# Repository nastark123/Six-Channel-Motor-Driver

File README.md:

# Six-Channel-Motor-Driver
Design files for six channel motor driver.

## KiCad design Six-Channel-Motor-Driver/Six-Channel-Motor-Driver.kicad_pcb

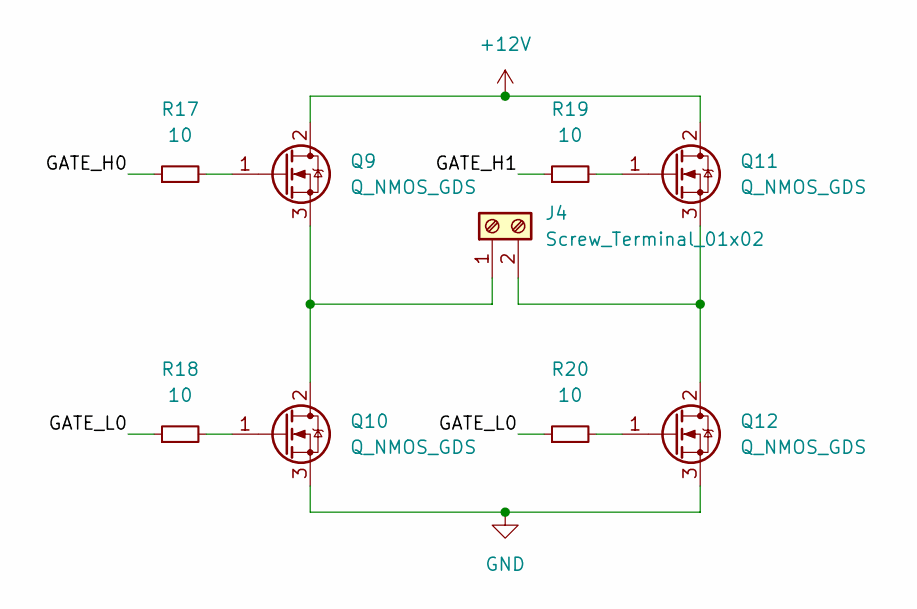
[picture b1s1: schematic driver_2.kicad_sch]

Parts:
J4: Screw_Terminal_01x02; SolderWire-2.5sqmm_1x02_P8.8mm_D2.4mm_OD4.4mm
Q9, Q10, Q11, Q12: Q_NMOS_GDS; SOT-23
R17, R18, R19, R20: 10; R_0603_1608Metric

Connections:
+12V: Q9.2 (D), Q11.2 (D); also elsewhere on the board
/Driver 2/GATE_H0: R17.1
/Driver 2/GATE_H1: R19.1
/Driver 2/GATE_L0: R18.1, R20.1
GND: Q10.3 (S), Q12.3 (S); also elsewhere on the board
unnamed: J4.1, Q9.3 (S), Q10.2 (D)
unnamed: J4.2, Q11.3 (S), Q12.2 (D)
unnamed: Q9.1 (G), R17.2
unnamed: Q10.1 (G), R18.2
unnamed: Q11.1 (G), R19.2
unnamed: Q12.1 (G), R20.2

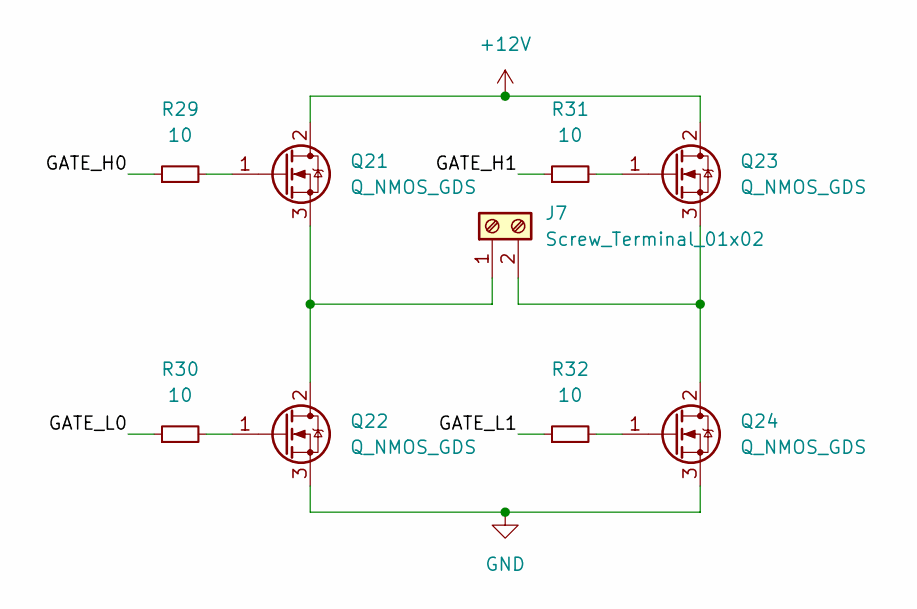
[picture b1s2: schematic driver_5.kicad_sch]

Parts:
J7: Screw_Terminal_01x02; SolderWire-2.5sqmm_1x02_P8.8mm_D2.4mm_OD4.4mm
Q21, Q22, Q23, Q24: Q_NMOS_GDS; SOT-23
R29, R30, R31, R32: 10; R_0603_1608Metric

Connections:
+12V: Q21.2 (D), Q23.2 (D); also elsewhere on the board
/Driver 5/GATE_H0: R29.1
/Driver 5/GATE_H1: R31.1
/Driver 5/GATE_L0: R30.1
/Driver 5/GATE_L1: R32.1
GND: Q22.3 (S), Q24.3 (S); also elsewhere on the board
unnamed: J7.1, Q21.3 (S), Q22.2 (D)
unnamed: J7.2, Q23.3 (S), Q24.2 (D)
unnamed: Q21.1 (G), R29.2
unnamed: Q22.1 (G), R30.2
unnamed: Q23.1 (G), R31.2
unnamed: Q24.1 (G), R32.2

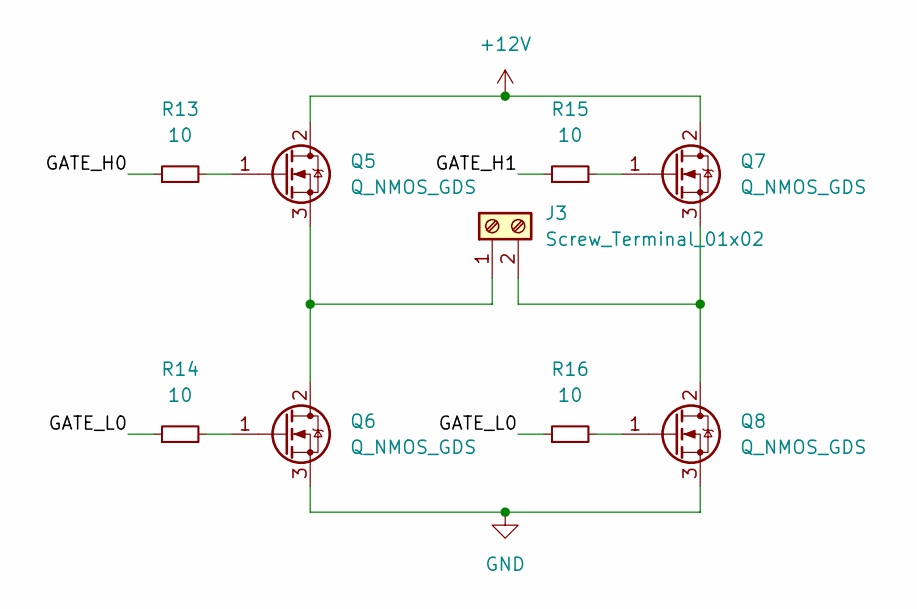
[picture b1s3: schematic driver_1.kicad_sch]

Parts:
J3: Screw_Terminal_01x02; SolderWire-2.5sqmm_1x02_P8.8mm_D2.4mm_OD4.4mm
Q5, Q6, Q7, Q8: Q_NMOS_GDS; SOT-23
R13, R14, R15, R16: 10; R_0603_1608Metric

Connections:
+12V: Q5.2 (D), Q7.2 (D); also elsewhere on the board
/Driver 1/GATE_H0: R13.1
/Driver 1/GATE_H1: R15.1
/Driver 1/GATE_L0: R14.1, R16.1
GND: Q6.3 (S), Q8.3 (S); also elsewhere on the board
unnamed: J3.1, Q5.3 (S), Q6.2 (D)
unnamed: J3.2, Q7.3 (S), Q8.2 (D)
unnamed: Q5.1 (G), R13.2
unnamed: Q6.1 (G), R14.2
unnamed: Q7.1 (G), R15.2
unnamed: Q8.1 (G), R16.2

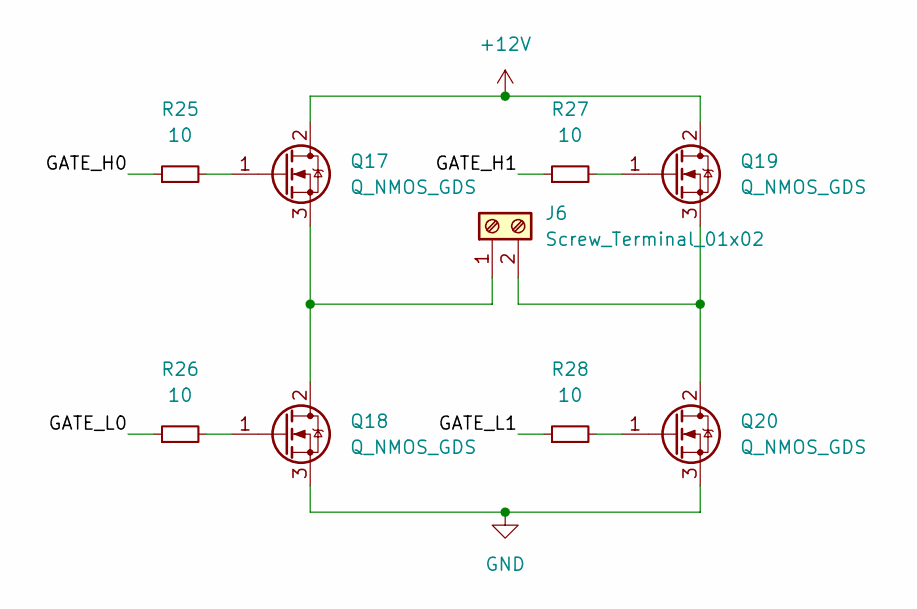
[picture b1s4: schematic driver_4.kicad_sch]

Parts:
J6: Screw_Terminal_01x02; SolderWire-2.5sqmm_1x02_P8.8mm_D2.4mm_OD4.4mm
Q17, Q18, Q19, Q20: Q_NMOS_GDS; SOT-23
R25, R26, R27, R28: 10; R_0603_1608Metric

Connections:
+12V: Q17.2 (D), Q19.2 (D); also elsewhere on the board
/Driver 4/GATE_H0: R25.1
/Driver 4/GATE_H1: R27.1
/Driver 4/GATE_L0: R26.1
/Driver 4/GATE_L1: R28.1
GND: Q18.3 (S), Q20.3 (S); also elsewhere on the board
unnamed: J6.1, Q17.3 (S), Q18.2 (D)
unnamed: J6.2, Q19.3 (S), Q20.2 (D)
unnamed: Q17.1 (G), R25.2
unnamed: Q18.1 (G), R26.2
unnamed: Q19.1 (G), R27.2
unnamed: Q20.1 (G), R28.2

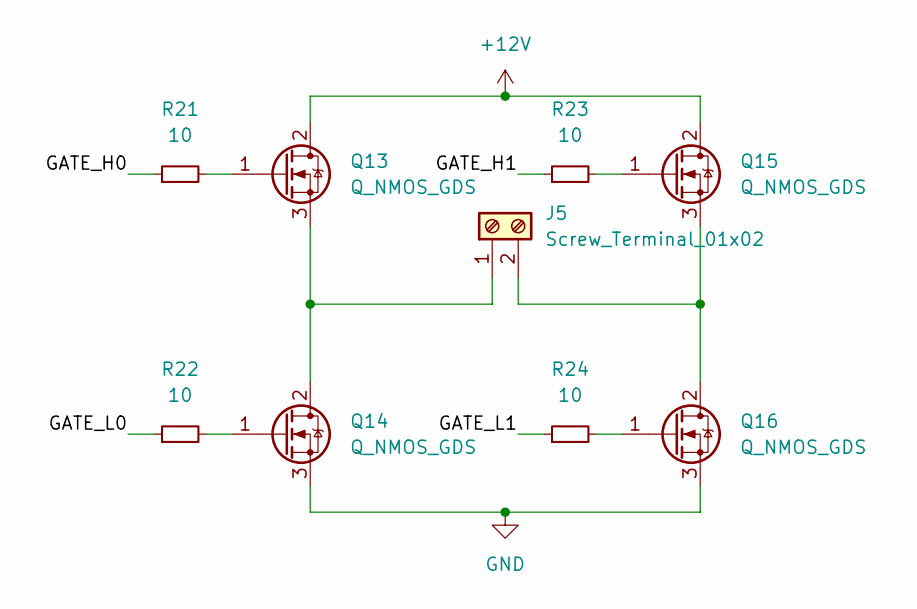
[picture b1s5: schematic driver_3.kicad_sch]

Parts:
J5: Screw_Terminal_01x02; SolderWire-2.5sqmm_1x02_P8.8mm_D2.4mm_OD4.4mm
Q13, Q14, Q15, Q16: Q_NMOS_GDS; SOT-23
R21, R22, R23, R24: 10; R_0603_1608Metric

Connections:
+12V: Q13.2 (D), Q15.2 (D); also elsewhere on the board
/Driver 3/GATE_H0: R21.1
/Driver 3/GATE_H1: R23.1
/Driver 3/GATE_L0: R22.1
/Driver 3/GATE_L1: R24.1
GND: Q14.3 (S), Q16.3 (S); also elsewhere on the board
unnamed: J5.1, Q13.3 (S), Q14.2 (D)
unnamed: J5.2, Q15.3 (S), Q16.2 (D)
unnamed: Q13.1 (G), R21.2
unnamed: Q14.1 (G), R22.2
unnamed: Q15.1 (G), R23.2
unnamed: Q16.1 (G), R24.2

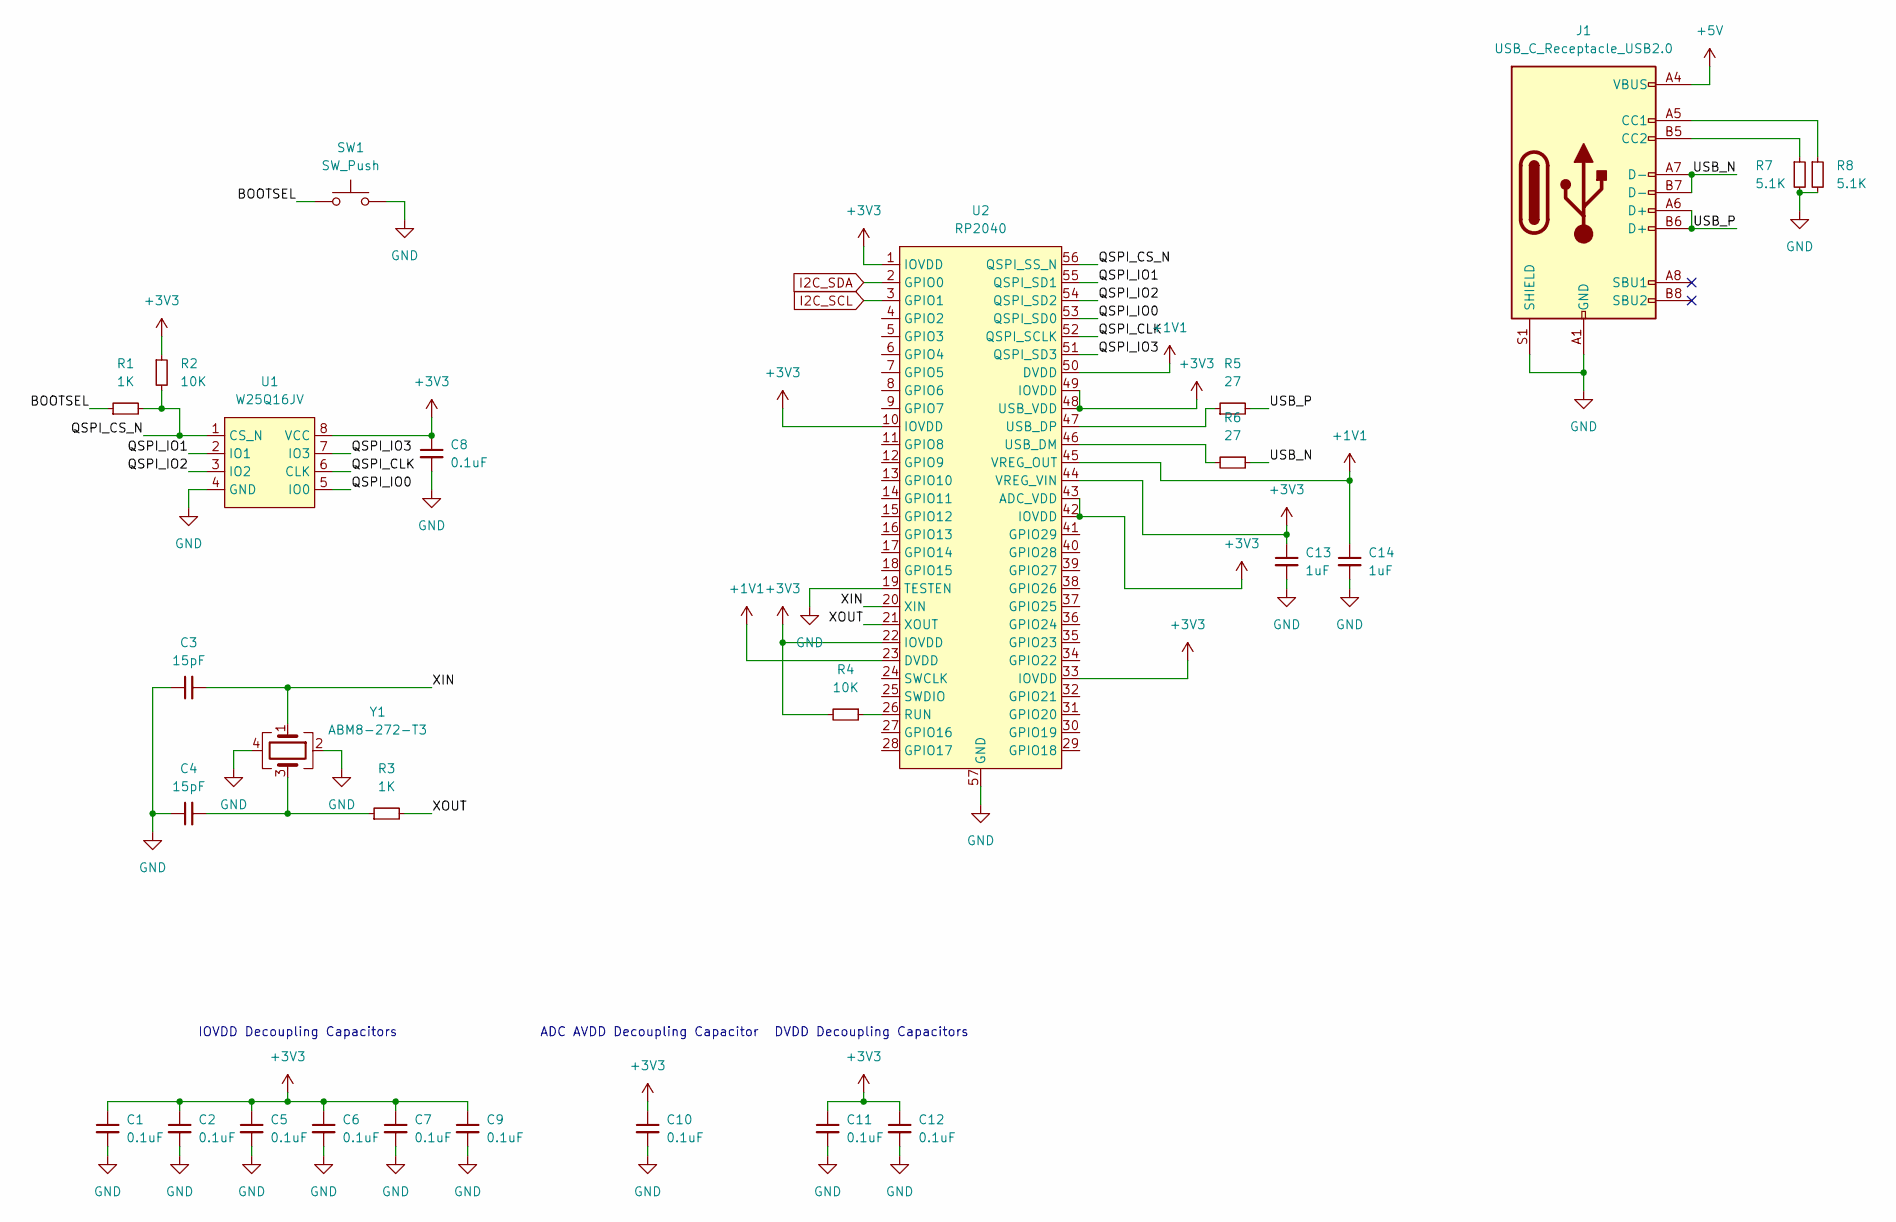
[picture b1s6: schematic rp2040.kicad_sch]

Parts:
C1, C2, C5, C6, C7, C8, C9, C10, C11, C12: 0.1uF; C_0603_1608Metric
C3, C4: 15pF; C_0603_1608Metric
C13, C14: 1uF; C_0603_1608Metric
J1: USB_C_Receptacle_USB2.0; USB_C_Receptacle_Molex_105450-0101
R1, R3: 1K; R_0603_1608Metric
R2, R4: 10K; R_0603_1608Metric
R5, R6: 27; R_0603_1608Metric
R7, R8: 5.1K; R_0603_1608Metric
SW1: SW_Push; SW_SPST_FSMSM
U1: W25Q16JV; SOIC-8_3.9x4.9mm_P1.27mm
U2: RP2040; QFN-56-1EP_7x7mm_P0.4mm_EP3.2x3.2mm
Y1: ABM8-272-T3; Oscillator_SMD_Abracon_ASE-4Pin_3.2x2.5mm

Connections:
+1V1: C14.1, U2.23 (DVDD), U2.45 (VREG_OUT), U2.50 (DVDD)
+3V3: C1.1, C2.1, C5.1, C6.1, C7.1, C8.1, C9.1, C10.1, C11.1, C12.1, C13.1, R2.1, R4.2, U1.8 (VCC), U2.1 (IOVDD), U2.10 (IOVDD), U2.22 (IOVDD), U2.33 (IOVDD), U2.42 (IOVDD), U2.43 (ADC_VDD), U2.44 (VREG_VIN), U2.48 (USB_VDD), U2.49 (IOVDD)
+5V: J1.A4 (VBUS), J1.A9 (VBUS), J1.B4 (VBUS), J1.B9 (VBUS)
/RP2040/BOOTSEL: R1.1, SW1.1
/RP2040/QSPI_CLK: U1.6 (CLK), U2.52 (QSPI_SCLK)
/RP2040/QSPI_CS_N: R1.2, R2.2, U1.1 (CS_N), U2.56 (QSPI_SS_N)
/RP2040/QSPI_IO0: U1.5 (IO0), U2.53 (QSPI_SD0)
/RP2040/QSPI_IO1: U1.2 (IO1), U2.55 (QSPI_SD1)
/RP2040/QSPI_IO2: U1.3 (IO2), U2.54 (QSPI_SD2)
/RP2040/QSPI_IO3: U1.7 (IO3), U2.51 (QSPI_SD3)
/RP2040/USB_N: J1.A7 (D-), J1.B7 (D-), R6.1
/RP2040/USB_P: J1.A6 (D+), J1.B6 (D+), R5.2
/RP2040/XIN: C3.2, U2.20 (XIN), Y1.1
/RP2040/XOUT: R3.2, U2.21 (XOUT)
GND: C1.2, C2.2, C3.1, C4.1, C5.2, C6.2, C7.2, C8.2, C9.2, C10.2, C11.2, C12.2, C13.2, C14.2, J1.A1 (GND), J1.A12 (GND), J1.B1 (GND), J1.B12 (GND), J1.S1 (SHIELD), R7.2, R8.2, SW1.2, U1.4 (GND), U2.19 (TESTEN), U2.57 (GND), Y1.2, Y1.4; also elsewhere on the board
I2C_SCL: U2.3 (GPIO1)
I2C_SDA: U2.2 (GPIO0)
unnamed: C4.2, R3.1, Y1.3
unnamed: J1.A5 (CC1), R8.1
unnamed: J1.B5 (CC2), R7.1
unnamed: R4.1, U2.26 (RUN)
unnamed: R5.1, U2.47 (USB_DP)
unnamed: R6.2, U2.46 (USB_DM)

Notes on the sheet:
IOVDD Decoupling Capacitors
ADC AVDD Decoupling Capacitor
DVDD Decoupling Capacitors

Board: 2 copper layers, 81 parts (0 on the bottom side), 60 nets, no tracks yet.

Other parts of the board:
J2: Screw_Terminal_01x02; SolderWire-2.5sqmm_1x02_P8.8mm_D2.4mm_OD4.4mm
Q1, Q2, Q3, Q4: Q_NMOS_GDS; SOT-23
R9, R10, R11, R12: 10; R_0603_1608Metric

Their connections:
+12V: Q1.2 (D), Q3.2 (D); also elsewhere on the board
GND: Q2.3 (S), Q4.3 (S); also elsewhere on the board
unnamed: J2.1, Q1.3 (S), Q2.2 (D)
unnamed: J2.2, Q3.3 (S), Q4.2 (D)
unnamed: Q1.1 (G), R9.2
unnamed: Q2.1 (G), R10.2
unnamed: Q3.1 (G), R11.2
unnamed: Q4.1 (G), R12.2

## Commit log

2024-05-04 Started work on MCU portion of design
2024-05-05 More work on MCU schematic
2024-05-07 Added start of driver blocks
